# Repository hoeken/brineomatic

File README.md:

This is the hardware design repository for Brineomatic.

For detailed documentation, please visit the [Brineomatic documentation](https://brineomatic.com).

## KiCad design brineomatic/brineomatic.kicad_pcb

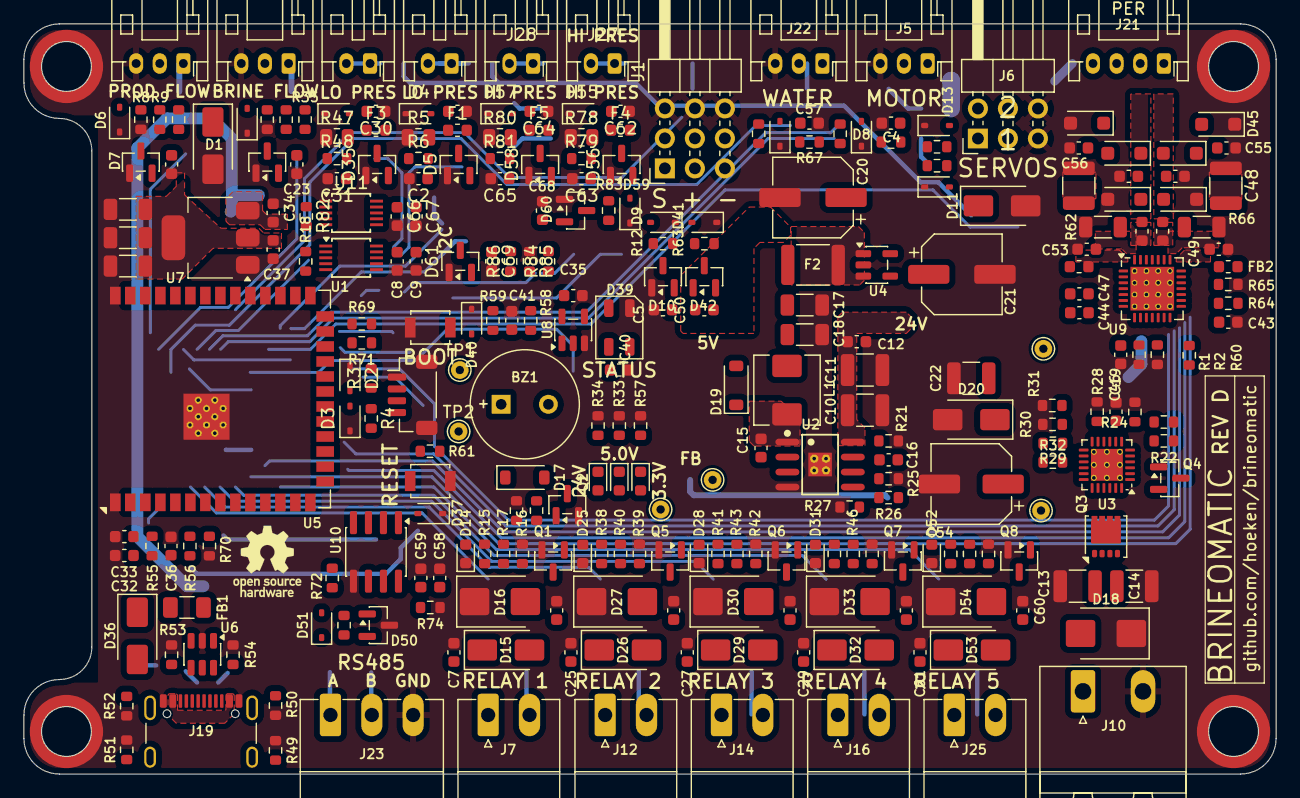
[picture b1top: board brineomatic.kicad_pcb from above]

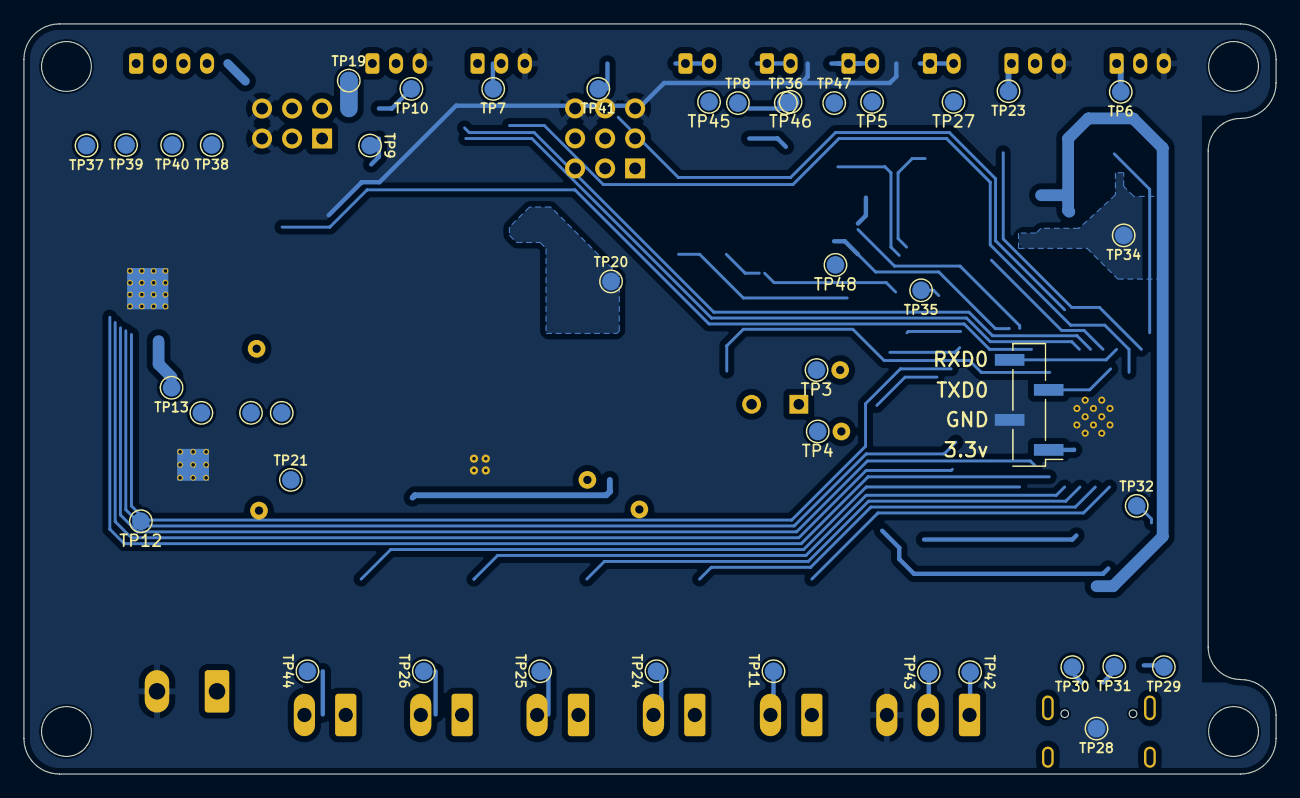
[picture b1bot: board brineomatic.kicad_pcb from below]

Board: 4 copper layers, 106.0 x 63.5 mm, 323 parts (43 on the bottom side), 132 nets.

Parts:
BZ1: Buzzer; MagneticBuzzer_QMB-09B-03
C1, C4, C6, C7, C24, C25, C26, C27, C28, C29, C30, C34, C36, C41, C57, C60, C61, C62, C64: 1uF; C_0603_1608Metric
C2, C5, C8, C12, C15, C19, C31, C33, C35, C40, C43, C44, C49, C50, C53, C59, C63, C65, C66, C68, C69: 100nF; C_0603_1608Metric
C3, C16, C23: 2.7nF; C_0603_1608Metric
C9, C58, C67: 10uF; C_0603_1608Metric
C10, C11, C13, C14, C22, C45, C48: 10uF; C_1210_3225Metric
C17, C18: 22uF; C_1206_3216Metric
C20, C21: 220uF / 16v; CP_Elec_6.3x5.4
C32: 22uF; C_0603_1608Metric
C37, C46: 4.7uF; C_0603_1608Metric
C38, C39, C42: 100uF / 6.3v; C_1206_3216Metric
C47: 22nF / 50v; C_0603_1608Metric
C51, C52, C55, C56: 470pf / 100v; C_0603_1608Metric
C54: 100uF / 35v; CP_Elec_6.3x7.7
D1, D11: SMAJ5.0A; D_SMA
D2, D3, D4, D6, D8, D9, D12, D13, D23, D34, D37, D40, D41, D49, D55, D57, D59: PESD3V3L1BA; D_SOD-323
D5, D10, D35, D42, D56, D58, D60, D61: BAV199; SOT-23
D7, D24: BAT54S; SOT-23
D14, D21, D22, D25, D28, D31, D38, D52: GREEN; LED_0603_1608Metric
D15, D20, D26, D29, D32, D53: SS54; D_SMA
D16, D18, D27, D30, D33, D54: SMBJ30CA; D_SMB
D17: B5819W; D_SOD-123
D19: 1N4148W; D_SOD-123
D36: SS34; D_SMA
D39: WS2812B-Mini; LED_WS2812B-Mini_PLCC4_3.5x3.5mm
D43, D44, D45, D46, D47, D48: SMF30CA; D_SOD-123F
D50: PSM712; SOT-23
D51: PSD12C; D_SOD-323
F1, F3, F4, F5: 30mA / 30v; Fuse_0603_1608Metric
F2: mSMD260; Fuse_1812_4532Metric
FB1: 1.5A; Fuse_1206_3216Metric
FB2, FB3, FB4, FB5: 50ohm @ 100mhz; L_0603_1608Metric
H1, H2, H3, H4: Standoff; SMTSO30XXX
J1: Conn_03x03; PinHeader_3x03_P2.54mm_Horizontal
J2: Conn_01x04_MountingPin; JST_SH_BM04B-SRSS-TB_1x04-1MP_P1.00mm_Vertical
J3, J18, J27, J28: JST_PH_S2B-PH-K_1x02_P2.00mm_Horizontal
J4, J5, J11, J22: JST_PH_S3B-PH-K_1x03_P2.00mm_Horizontal
J6: PinHeader_2x03_P2.54mm_Horizontal
J7, J12, J14, J16, J25: 3.5MM; PhoenixContact_MC_1,5_2-G-3.5_1x02_P3.50mm_Horizontal
J10: 5.08MM; PhoenixContact_MSTBA_2,5_2-G-5,08_1x02_P5.08mm_Horizontal
J19: USB_TYPE_C_16PIN; USB_C_Receptacle_GCT_USB4105-xx-A_16P_TopMnt_Horizontal
J20: Conn_01x04; PinHeader_1x04_P2.54mm_Vertical_SMD_Pin1Left
J21: Conn_01x04; JST_PH_S4B-PH-K_1x04_P2.00mm_Horizontal
J23: 3.5mm; PhoenixContact_MC_1,5_3-G-3.5_1x03_P3.50mm_Horizontal
L1: 6.8uH; L_Chilisin_BMRA00050530
Q1, Q2, Q5, Q6, Q7, Q8: Si2318; SOT-23
Q3: CSD19537Q3; VSON-8_3.3x3.3mm_P0.65mm_NexFET
Q4: BSS138; SOT-23
R1, R2, R6, R12, R16, R18, R20, R33, R39, R42, R45, R48, R56, R59, R63, R65, R69, R70, R71, R76, R79, R81, R82, R83, R86: 10k; R_0603_1608Metric
R3, R4, R8, R36: 2.2k; R_0603_1608Metric
R5, R47, R78, R80: 100R 0.1%; R_0805_2012Metric
R7, R35: 1.2K; R_0603_1608Metric
R9, R10, R37, R67: 4.7K; R_0603_1608Metric
R11, R13, R14, R55, R58, R68: 100R; R_0603_1608Metric
R15, R38, R41, R44, R60, R75: 1k; R_0603_1608Metric
R17, R19, R40, R43, R46, R77: 220R; R_0603_1608Metric
R21: 82k 1%; R_0603_1608Metric
R22: 820k 1%; R_0603_1608Metric
R23: 90.9k 1%; R_0603_1608Metric
R24, R31: 34k 1%; R_0603_1608Metric
R25, R32: 24k; R_0603_1608Metric
R26: 62k 1%; R_0603_1608Metric
R27: 11.8k 1%; R_0603_1608Metric
R28: 4.53k 1%; R_0603_1608Metric
R29: 383k 1%; R_0603_1608Metric
R30: 56k 1%; R_0603_1608Metric
R34: 100k; R_0603_1608Metric
R49, R50, R51, R52: 0R; R_0603_1608Metric
R53, R54, R57: 5.1k; R_0603_1608Metric
R61, R64, R72, R74: 20k; R_0603_1608Metric
R62, R66: 0.11R 1%; R_1206_3216Metric
R73: 120R; R_0603_1608Metric
R84: 300K 0.1%; R_0603_1608Metric
R85: 22K 0.1%; R_0603_1608Metric
SW1, SW2: SW_SPST_B3U-1000P
SYM1: Logo_Open_Hardware_Small; OSHW-Logo_5.7x6mm_SilkScreen
TP1, TP2, TP14, TP18, TP22, TP33: TestPoint_THTPad_D1.5mm_Drill0.7mm
TP3, TP4, TP5, TP6, TP7, TP8, TP9, TP10, TP11, TP12, TP13, TP15, TP16, TP17, TP19, TP20, TP21, TP23, TP24, TP25, TP26, TP27, TP28, TP29, TP30, TP31, TP32, TP34, TP35, TP36, TP37, TP38, TP39, TP40, TP41, TP42, TP43, TP44, TP45, TP46, TP47, TP48: TestPoint; TestPoint_Pad_D1.5mm
U1, U11: ADS1115IDGSR; TSSOP-10_3x3mm_P0.5mm
U2: RT7272BGSP; SOIC-8_L5.0-W4.0-P1.27-LS6.0-BL-EP2.0
U3: TPS26630RGE; QFN-24-1EP_4x4mm_P0.5mm_EP2.7x2.7mm_ThermalVias
U4: MAX40200AUK; SOT-23-5
U5: ESP32-S3-WROOM-1-N16R8; ESP32-S3-WROOM-1
U6: USBLC6-2SC6; SOT-23-6
U7: LDL1117S33R; SOT-223-3_TabPin2
U8: SN74LV1T34DBV; SOT-23-5
U9: TMC2209-LA; VQFN-28-1EP_5x5mm_P0.5mm_EP3.7x3.7mm_ThermalVias
U10: MAX3485; SOIC-8_3.9x4.9mm_P1.27mm

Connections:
5V_HIGH_POWER: C20.1, D11.1 (A1), F2.1, J6.3, J6.4, TP19.1, U4.1 (VDD), U4.3 (EN)
+3.3V: BZ1.1 (+), C4.1, C8.1, C9.1, C32.1, C33.1, C37.1, C38.1, C39.1, C42.1, C43.1, C57.1, C58.1, C59.1, C66.1, C67.1, D5.2 (K), D7.2 (K), D10.2 (K), D17.1 (K), D24.2 (K), D35.2 (K), D38.2 (A), D42.2 (K), D56.2 (K), D58.2 (K), D60.2 (K), D61.2 (K), J2.2, J5.1, J20.1, J22.1, R3.2, R4.2, R10.2, R18.2, R56.1, R59.2, R61.1, R67.2, R69.2, R71.2, R72.2, R82.2, TP33.1, TP34.1, U1.1 (ADDR), U1.8 (VDD), U5.2 (3V3), U7.2 (VO), U9.15 (VCC_IO), U10.8 (VCC), U11.8 (VDD)
+5V: C21.1, C34.1, C35.1, C40.1, D1.1 (A1), D21.2 (A), D39.1 (VDD), FB1.2, J1.2, J1.5, J1.8, J4.1, J11.1, R7.2, R35.2, TP20.1, TP22.1, U4.5 (OUT), U7.3 (VI), U8.5 (VCC)
+24V: C7.2, C10.1, C11.1, C12.1, C22.2, C25.2, C27.2, C29.2, C44.2, C45.1, C48.1, C49.2, C53.2, C54.1, C61.2, D15.1 (K), D20.1 (K), D22.2 (A), D26.1 (K), D29.1 (K), D32.1 (K), D53.1 (K), F1.2, F3.2, F4.2, F5.2, J7.1, J12.1, J14.1, J16.1, J25.1, R29.1, R32.1, R84.2, TP18.1, TP21.1, U2.8 (VIN), U3.17 (OUT), U3.18 (OUT), U9.22 (VS), U9.28 (VS)
/ADC1/ADC0: C68.1, D60.3 (COM), R83.2, U1.4 (AIN0)
/ADC1/ADC1: C5.1, D10.3 (COM), R12.2, U1.5 (AIN1)
/ADC1/ADC2: C50.1, D42.3 (COM), R63.2, U1.6 (AIN2)
/ADC1/ADC3: C69.1, D61.3 (COM), R86.2, TP48.1, U1.7 (AIN3)
/ADC2/ADC0: C31.1, D35.3 (COM), R48.2, U11.4 (AIN0)
/ADC2/ADC1: C2.1, D5.3 (COM), R6.2, U11.5 (AIN1)
/ADC2/ADC2: C65.1, D58.3 (COM), R81.2, U11.6 (AIN2)
/ADC2/ADC3: C63.1, D56.3 (COM), R79.2, U11.7 (AIN3)
/ESP32-S3/CC1_1: J19.A5 (CC1), R53.1
/ESP32-S3/CC2_1: J19.B5 (CC2), R54.1
/ESP32-S3/EN: R55.2, TP32.1, U5.3 (EN)
/ESP32-S3/ESP_RXD0: J20.4, U5.36 (RXD0)
/ESP32-S3/ESP_TXD0: J20.3, U5.37 (TXD0)
/ESP32-S3/ESP_USB+: U5.14 (USB_D+), U6.1 (I/O1)
/ESP32-S3/ESP_USB-: U5.13 (USB_D-), U6.3 (I/O2)
/ESP32-S3/GPIO0_BOOT: R58.2, TP35.1, U5.27 (IO0)
/ESP32-S3/GPIO38: U5.31 (IO38), U8.2 (A)
/ESP32-S3/USB_D+: J19.A6 (D+), J19.B6 (D+), TP30.1, U6.6 (I/O1)
/ESP32-S3/USB_D-: J19.A7 (D-), J19.B7 (D-), TP31.1, U6.4 (I/O2)
/ESP32-S3/VBUS: D36.2 (A), J19.A4 (VBUS), J19.A9 (VBUS), J19.B4 (VBUS), J19.B9 (VBUS), TP29.1, U6.5 (VBUS)
/Power Supply/PRE_24: C13.2, C14.2, D18.2 (A2), J10.1, Q3.1 (S), Q3.2 (S), Q3.3 (S), Q4.2 (S), R22.1, TP12.1, TP13.1, U3.5 (IN_SYS)
/Power Supply/SW: C15.2, L1.1, U2.1 (SW)
/Stepper Driver/MS1: R1.1, U9.9 (MS1/AD0)
/Stepper Driver/MS2: R2.1, U9.10 (MS2/AD1)
/Stepper Driver/OA1: FB3.1, U9.24 (OA1)
/Stepper Driver/OA2: FB2.1, U9.21 (OA2)
/Stepper Driver/OB1: FB4.1, U9.26 (OB1)
/Stepper Driver/OB2: FB5.1, U9.1 (OB2)
ADC1_ALERT: R18.1, U1.2 (ALERT/RDY), U5.35 (IO42)
ADC2_ALERT: R82.1, U5.15 (IO3), U11.2 (ALERT/RDY)
BRINE_FLOWMETER: C23.1, D24.3 (COM), R37.2, U5.38 (IO2)
BRINE_TDS: D41.2 (A2), J1.7, R63.1, TP36.1
BUZZER: R19.2, U5.22 (IO14)
GND: C1.1, C2.2, C3.2, C4.2, C5.2, C6.1, C7.1, C8.2, C9.2, C10.2, C11.2, C12.2, C13.1, C14.1, C17.2, C18.2, C19.2, C20.2, C21.2, C22.1, C23.2, C24.1, C25.1, C26.1, C27.1, C28.1, C29.1, C30.1, C31.2, C32.2, C33.2, C34.2, C35.2, C36.2, C37.2, C38.2, C39.2, C40.2, C41.1, C42.2, C43.2, C45.2, C46.2, C48.2, C49.1, C50.2, C51.1, C52.2, C53.1, C54.2, C55.1, C56.2, C57.2, C58.2, C59.2, C60.1, C61.1, C62.1, C63.2, C64.1, C65.2, C66.2, C67.2, C68.2, C69.2, D1.2 (A2), D2.1 (A1), D3.1 (A1), D4.1 (A1), D5.1 (A), D6.1 (A1), D7.1 (A), D8.1 (A1), D9.1 (A1), D10.1 (A), D11.2 (A2), D12.1 (A1), D13.1 (A1), D14.1 (K), D16.1 (A1), D18.1 (A1), D20.2 (A), D23.1 (A1), D24.1 (A), D25.1 (K), D27.1 (A1), D28.1 (K), D30.1 (A1), D31.1 (K), D33.1 (A1), D34.1 (A1), D35.1 (A), D37.1 (A1), D39.3 (VSS), D40.1 (A1), D41.1 (A1), D42.1 (A), D43.1 (A1), D44.2 (A2), D45.1 (A1), D48.2 (A2), D49.1 (A1), D50.3 (common), D52.1 (K), D54.1 (A1), D55.1 (A1), D56.1 (A), D57.1 (A1), D58.1 (A), D59.1 (A1), D60.1 (A), D61.1 (A), H1.1, H2.1, H3.1, H4.1, J1.3, J1.6, J1.9, J2.1, J2.MP (MountPin), J4.3, J5.3, J6.5, J6.6, J10.2, J11.3, J19.A1 (GND), J19.A12 (GND), J19.B1 (GND), J19.B12 (GND), J20.2, J22.3, J23.3, Q1.2 (S), Q2.2 (S), Q5.2 (S), Q6.2 (S), Q7.2 (S), Q8.2 (S), R1.2, R2.2, R5.1, R8.1, R16.1, R20.2, R21.2, R24.2, R25.2, R27.2, R28.2, R30.2, R31.2, R33.2, R34.2, R36.1, R39.1, R42.1, R45.1, R47.1, R49.1, R50.1, R51.1, R52.1, R53.2, R54.2, R57.2, R62.1, R65.1, R66.2, R70.1, R74.1, R76.1, R78.1, R80.1, R85.1, SW1.2, SW2.2, TP28.1, U1.3 (GND), U2.4 (GND), U3.8 (GND), U3.11 (MODE), U3.25 (GND), U4.2 (GND), U5.1 (GND), U5.40 (GND), U5.41 (GND), U6.2 (GND), U7.1 (GND), U8.3 (GND), U9.3 (GND), U9.13 (CLK), U9.18 (GND), U9.20 (STDBY), U9.25 (NC), U9.29 (GND), U10.5 (GND), U11.1 (ADDR), U11.3 (GND)
MOTOR_TEMPERATURE: R11.1, U5.4 (IO4)
unnamed: BZ1.2 (-), D17.2 (A), Q2.3 (D)
unnamed: C16.1, R25.1
unnamed: D4.2 (A2), J3.2, R5.2, R6.1, TP5.1
unnamed: D6.2 (A2), J4.2, R7.1, R8.2, R9.1, TP6.1
unnamed: D8.2 (A2), J5.2, R10.1, R11.2, TP7.1
unnamed: D12.2 (A2), J6.1, R13.1, TP9.1
unnamed: D13.2 (A2), J6.2, R14.2, TP10.1
unnamed: D14.2 (A), R15.1
unnamed: C6.2, D15.2 (A), D16.2 (A2), J7.2, Q1.3 (D), TP11.1
unnamed: C17.1, C18.1, D19.2 (A), F2.2, L1.2, R26.1, TP14.1
unnamed: C15.1, D19.1 (K), U2.2 (BOOT)
unnamed: D21.1 (K), R33.1
unnamed: D22.1 (K), R34.1
unnamed: D23.2 (A2), J11.2, R35.1, R36.2, R37.1, TP23.1
unnamed: D25.2 (A), R38.1
unnamed: C24.2, D26.2 (A), D27.2 (A2), J12.2, Q5.3 (D), TP24.1
unnamed: D28.2 (A), R41.1
unnamed: C26.2, D29.2 (A), D30.2 (A2), J14.2, Q6.3 (D), TP25.1
unnamed: D31.2 (A), R44.1
unnamed: C28.2, D32.2 (A), D33.2 (A2), J16.2, Q7.3 (D), TP26.1
unnamed: D34.2 (A2), J18.2, R47.2, R48.1, TP27.1
unnamed: D36.1 (K), FB1.1
unnamed: C36.1, D37.2 (A2), R55.1, R56.2, SW1.1
unnamed: D38.1 (K), R57.1
unnamed: D39.4 (DIN), U8.4 (Y)
unnamed: C41.2, D40.2 (A2), R58.1, R59.1, SW2.1
unnamed: C51.2, D43.2 (A2), D46.2 (A2), FB3.2, J21.2, TP39.1
unnamed: C52.1, D44.1 (A1), D47.1 (A1), FB4.2, J21.3, TP40.1
unnamed: C55.2, D45.2 (A2), D46.1 (A1), FB2.2, J21.1, TP37.1
unnamed: C56.1, D47.2 (A2), D48.1 (A1), FB5.2, J21.4, TP38.1
unnamed: D49.2 (A2), J22.2, R67.1, R68.2, TP41.1
unnamed: D50.1 (A1), D51.2 (A2), J23.1, R72.1, R73.2, TP42.1, U10.6 (A)
unnamed: D50.2 (A2), D51.1 (A1), J23.2, R73.1, R74.2, TP43.1, U10.7 (B)
unnamed: D52.2 (A), R75.1
unnamed: C60.2, D53.2 (A), D54.2 (A2), J25.2, Q8.3 (D), TP44.1
unnamed: D55.2 (A2), J27.2, R78.2, R79.1, TP45.1
unnamed: D57.2 (A2), J28.2, R80.2, R81.1, TP46.1
unnamed: C1.2, F1.1, J3.1
unnamed: C30.2, F3.1, J18.1
unnamed: J19.S1 (SHIELD), R49.2, R50.2, R51.2, R52.2
unnamed: C62.2, F4.1, J27.1
unnamed: C64.2, F5.1, J28.1
unnamed: Q1.1 (G), R17.2
unnamed: Q2.1 (G), R19.1, R20.1
unnamed: Q3.5 (D), U3.1 (IN), U3.2 (IN)
unnamed: Q3.4 (G), Q4.3 (D), U3.3 (B_GATE)
unnamed: Q4.1 (G), U3.4 (DRV)
unnamed: Q5.1 (G), R40.2
unnamed: Q6.1 (G), R43.2
unnamed: Q7.1 (G), R46.2
unnamed: Q8.1 (G), R77.2
unnamed: R84.1, R85.2, R86.1
unnamed: C16.2, U2.6 (COMP)
unnamed: R26.2, R27.1, U2.5 (FB)
unnamed: R21.1, U2.7 (RLIM)
unnamed: R28.1, U3.10 (ILIM)
unnamed: R31.1, U3.13 (IMON)
unnamed: R23.2, R24.1, U3.7 (OVP)
unnamed: R29.2, R30.1, U3.15 (PGTH)
unnamed: R22.2, R23.1, U3.6 (UVLO)
unnamed: C19.1, U3.9 (dVdT)
unnamed: TP15.1, U3.14 (~FLT)
unnamed: TP16.1, U3.12 (~SHDN)
unnamed: C46.1, R64.2, U9.8 (5VOUT)
unnamed: R66.1, U9.23 (BRA)
unnamed: R62.2, U9.27 (BRB)
unnamed: C47.1, U9.5 (CPI)
unnamed: C47.2, U9.4 (CPO)
unnamed: C44.1, U9.6 (VCP)
unnamed: R64.1, R65.2, U9.17 (VREF)
PGOOD: R32.2, TP17.1, U2.3 (EN), U3.16 (PGOOD)
PRODUCT_FLOWMETER: C3.1, D7.3 (COM), R9.2, U5.39 (IO1)
PRODUCT_TDS: D9.2 (A2), J1.4, R12.1, TP8.1
RS485_DERE: R70.2, U5.5 (IO5), U10.2 (~RE), U10.3 (DE)
RS485_DI: R69.1, U5.25 (IO48), U10.4 (DI)
RS485_RO: R71.1, U5.24 (IO47), U10.1 (RO)
SCL: D3.2 (A2), J2.4, R4.1, TP2.1, TP4.1, U1.10 (SCL), U5.20 (IO12), U11.10 (SCL)
SDA: D2.2 (A2), J2.3, R3.1, TP1.1, TP3.1, U1.9 (SDA), U5.21 (IO13), U11.9 (SDA)
SERVO1: R13.2, U5.33 (IO40)
SERVO2: R14.1, U5.34 (IO41)
SOLENOID1: R15.2, R16.2, R17.1, U5.6 (IO6)
SOLENOID2: R38.2, R39.2, R40.1, U5.7 (IO7)
SOLENOID3: R41.2, R42.2, R43.1, U5.8 (IO15)
SOLENOID4: R44.2, R45.2, R46.1, U5.9 (IO16)
SOLENOID5: R75.2, R76.2, R77.1, U5.12 (IO8)
SOURCE_TDS: D59.2 (A2), J1.1, R83.1, TP47.1
TMC2209_DIAG: U5.23 (IO21), U9.11 (DIAG)
TMC2209_DIR: U5.11 (IO18), U9.19 (DIR)
TMC2209_EN: R61.2, U5.19 (IO11), U9.2 (~EN)
TMC2209_RX: R60.1, U5.17 (IO9)
TMC2209_STEP: U5.10 (IO17), U9.16 (STEP)
TMC2209_TX: R60.2, U5.18 (IO10), U9.14 (~PD/UART)
WATER_TEMPERATURE: R68.1, U5.32 (IO39)

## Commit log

2024-08-07 initial design work import
2024-10-04 rough first pass at the schematic.
2024-10-04 getting closer. added tds
2024-10-04 starting to shape up, footprints etc
2024-10-06 starting to look good.
2024-10-06 silkscreen and more layout tweaks.
2024-10-06 updated bom and prepping for Rev A
2024-10-06 updates parts, footprints, etc. ready for production.
2024-10-06 updated plumbing and overview schematics.
2024-10-23 started in on RevA testing
2024-10-25 added alert line to adc
2024-10-25 fixed bat54s placement.
2024-10-26 added piezo buzzer
2024-10-27 case design is finished.
2024-11-02 updated todo
2024-11-09 updated power wiring schematic
2024-11-26 added ui screenshot
2024-11-27 added more assets and bom script.
2024-11-27 Update README.md
    added images
2024-11-27 added rainman install photo.
2024-11-27 tidy up files.
2024-11-27 added step files.
2025-07-31 kicad v9 and updated todo.
2025-08-11 did a bunch of schematic work for Rev B
2025-08-11 worked on schematic and layout a bit more.
2025-08-13 lots of progress on Rev B
2025-08-13 first pass fully routed
2025-08-13 added fuse on 3.3v
2025-08-14 reverse polarity circuit added
2025-08-14 more work on the power circuitry
2025-08-14 stepstick headers updated.
2025-08-14 updated wiring and connector to match dfrobot for tds sensors
2025-08-14 moved to bom friendly stepper driver mount
2025-09-29 switched to onboard esp32-s3 and re-drew tmc2209 driver
2025-09-29 tmc2209 driver schematic checked and laid out nicely.
2025-09-29 single 5v supply works just fine
2025-09-30 updated board edges and general tweaks
2025-09-30 all the important parts have 3d models now.
2025-10-01 aligned all connectors with board edge
2025-10-01 fully routed and erc/drc passed
2025-10-01 removed the onboard fuse.
2025-10-01 re-added fuse, switched to 5x20mm
2025-10-02 silkscreen good and all drc errors fixed.
2025-10-02 worked on bom for rev b prototype run
2025-10-02 updated jlc parts rotations and placement offsets
2025-10-02 a few last minute routing tweaks
2025-10-02 copied back from esp32-s3-template
2025-10-02 via stitching, a couple minor changes, i think its ready for production
2025-10-02 piezo resistor
2025-10-04 added qwiic i2c connector
2025-10-05 added missing cap to reverse polarity protection circuit
2025-10-07 sent to production
2025-10-08 added case and schematic
2025-10-22 added bom
2025-11-06 updated the todo for a future rev c
2025-11-28 new logo who dis?
2025-11-28 big readme update for rev b
2025-11-28 Update README.md
    badges!
2025-11-28 added connector/pinout documentation for rev b board.
2025-11-28 added node red flow example
2025-11-28 added running mode
2025-11-28 Update README.md
    added some photos + node red docs
2025-11-28 Update README.md
    moved node-red
2025-11-28 cropped the pinout image.
2025-11-29 straightened board bottom edge
2025-11-29 added pullup resistor to adc alert
2025-11-29 changed mosfet pulldowns to 10k. moved 5v to esp32_5v to power everything over usb.
2025-11-29 added rs485 circuit
2025-11-29 added water temperature connector
2025-11-29 5v power supply is sorted.
2025-11-29 stacked tds, removed stepper vref, pulled in esp32-s3 schematic, added extra relay output
2025-11-29 added sendit piezo
2025-11-29 worked on component layout a bit more.
2025-11-29 all connectors are now flush withe 3mm outside edge of the case
2025-11-29 connector placement done
2025-11-29 updated running image
2025-11-30 schematic tidy, usb c position verified, component placement work.
2025-11-30 added voltage divider to vref. more component shuffling.
2025-11-30 power routing is done.
2025-12-01 board fully routed first pass.
2025-12-01 more esd protection, drc passing, silkscreen fixed
2025-12-02 layout tweaks
2025-12-02 via stitching plugin is sick
2025-12-02 bom and cpl file are good.
2025-12-02 removed rs485 jumper and added silkscreen
2025-12-02 small cleanups on schematic
2025-12-02 updated the 4-20ma sensor resistor value
2025-12-03 value and component updates
2025-12-03 added back up usb serial converter headers
2025-12-03 added missing gnd test point
2025-12-07 added more esd protection to the power rails (24v, 5v, 3.3v)
2025-12-07 removed old schematics
2025-12-07 ignoring production/ now.
2025-12-08 re-arranged pins to avoid boot glitches on solenoids
2025-12-08 sprinkled in a few more gnd vias
2025-12-09 left attachment points a bit biger
2025-12-09 switched to the LDL1117 ldo
2025-12-11 switch to rt7272b for 24v -> 5v regulator
2025-12-11 switched back to bigger capacitors after reading datasheet
2025-12-11 added bootstrap diode just in case
2025-12-11 added bulk cap to 5v rail and tidied silkscreen
2025-12-11 added a few missing datasheets, switched to new mosfet for buzzer to consolidate bom
2025-12-11 via stitching redo
2025-12-12 switched to bav199 on pressure / tds
2025-12-13 tested startup glitch with scope, didnt find anything. might have been my old code
2025-12-13 tested and update bom + placement
2025-12-13 silkscreen tweaks for legibility
2025-12-13 updated resistor p/ns in bom
2025-12-15 added esd protection to relay driver connector
2025-12-22 updated todo based on design review feedback
2025-12-22 put 2x0 ohm between GND and USB SHIELD
2025-12-22 add ESD and series resistor to GPIO0/EN
2025-12-22 tmc2209 add 470pF / 100v caps to outputs for esd protection
2025-12-22 improved stepper 24v routing
2025-12-22 updated the modbus schematic with esd and DERE combination
2025-12-22 change to 1.5A fuse on usb
2025-12-22 L2 -> 3.3v power plane
2025-12-22 add inline resistor to temperature sensor + servo inputs - 100ohm
2025-12-22 switch pulldown to before 220R on mosfets (no voltage divider)
2025-12-22 updated analog sensor esd schematic
2025-12-22 added bulk cap after ideal diode
2025-12-22 added more input/output caps
2025-12-22 added 1uF cap to pressure sensor connectors for esd
2025-12-22 voltage divider on EN pin to turn on at 10.2v (EN = 2v) -> connect to VIN not 24v
2025-12-22 5v reg routing
2025-12-22 cleaned up hierarchical pin settings
2025-12-22 tidied up the top level schematic
2025-12-22 holy re-routing batman. board is fully routed first pass.
2025-12-22 a couple placement and routing tweaks
2025-12-22 silkscreen fixed, vias stitched, getting close
2025-12-23 added test points
2025-12-23 unsaved schematic
2025-12-23 changed to tps26630 for power protection
2025-12-23 tps26630 layout is done.
2025-12-23 added schottky diode per datasheet
2025-12-23 silkscreen updated, drc passing
2025-12-23 datasheet double checking - updated RLIM value
2025-12-24 removed LC filter and various cleanup for rev c
2025-12-24 somehow managed to fit the whole ESD/EMI solution into the same stepper footprint.
2025-12-24 fixed silkscreen and vias and all other drc errors.
2025-12-24 bom and placement verified
2025-12-24 cleaned up some vias and ground planes a bit
2025-12-24 more power / gnd / via tweaks.
2025-12-25 cant believe i deleted the via stitching
2025-12-25 minor value tweak and ready for production
2025-12-25 vias off a tiny amount
2025-12-25 added Rev C changelog info
2026-01-06 * Fixed SMAJ5.0A symbols and footprint * Swapped L2 and L3. Now SIG/GND/PWR/SIG * Consolidated both temperature sensors to GPIO4
2026-01-08 Revert "* Fixed SMAJ5.0A symbols and footprint"
    This reverts commit 813d7f7220c8f38d0c15f44e401852de1da31e2a.
2026-01-08 Fixed SMAJ5.0A symbols and footprint
2026-01-08 Swapped L2 and L3. Now SIG/GND/PWR/SIG
2026-01-08 Fixed Water/Motor Temperature silkscreen mixup
2026-01-08 fixed a rename mistake between temp sensor signals
2026-01-08 Re-routed 5V to run through TVS first
2026-01-09 updated silkcreen with REV_C1
2026-01-09 increased amperage on F2 / 5v
2026-01-12 added lcsc p/n for fuse.
2026-01-23 added rev c pinout
2026-01-23 renamed diagram
2026-01-23 higher res pinout
2026-03-03 added rev c case
2026-03-22 Marked R67 (RS485 termination resistor) as DNP
2026-03-25 added schematic and pcba instructions
2026-03-25 added an example dashboard for home assistant.
2026-04-09 stubbed readme.
2026-04-09 micro tweak
2026-04-09 dont need to link to ourself
2026-04-09 updated link
2026-04-09 removed old files that live on the website now.
2026-04-10 Added the latest control panel update
2026-04-10 updated manufacturing instructions.
2026-04-12 moved diagrams to brineomatic-website
2026-05-05 updated rev d todo
2026-05-05 updated todo with more plan.
2026-05-07 bus voltage now.
2026-06-02 Updating schematic for Rev D: * Original ADS1115 * brine tds (same) * product tds (same) * bus voltage (new) * spare 4-20ma sensor (new)
    * Add 2nd ADS1115 -> only 4-20ma sensors
    * pre-filter pressure - jst 2.0
    * mid-filter pressure - jst 2.0
    * post-filter pressure - jst 2.0
    * high pressure - jst 2.0
    * alert pin -> gpio3
2026-06-02 updated changelog
2026-06-15 tds sensor input -> pin header 2.54 3x03
2026-06-15 removed fiducials + alignment holes
2026-06-15 * added 30ma PTC fuses to 24v line of pressure sensors * new part layout mostly done
